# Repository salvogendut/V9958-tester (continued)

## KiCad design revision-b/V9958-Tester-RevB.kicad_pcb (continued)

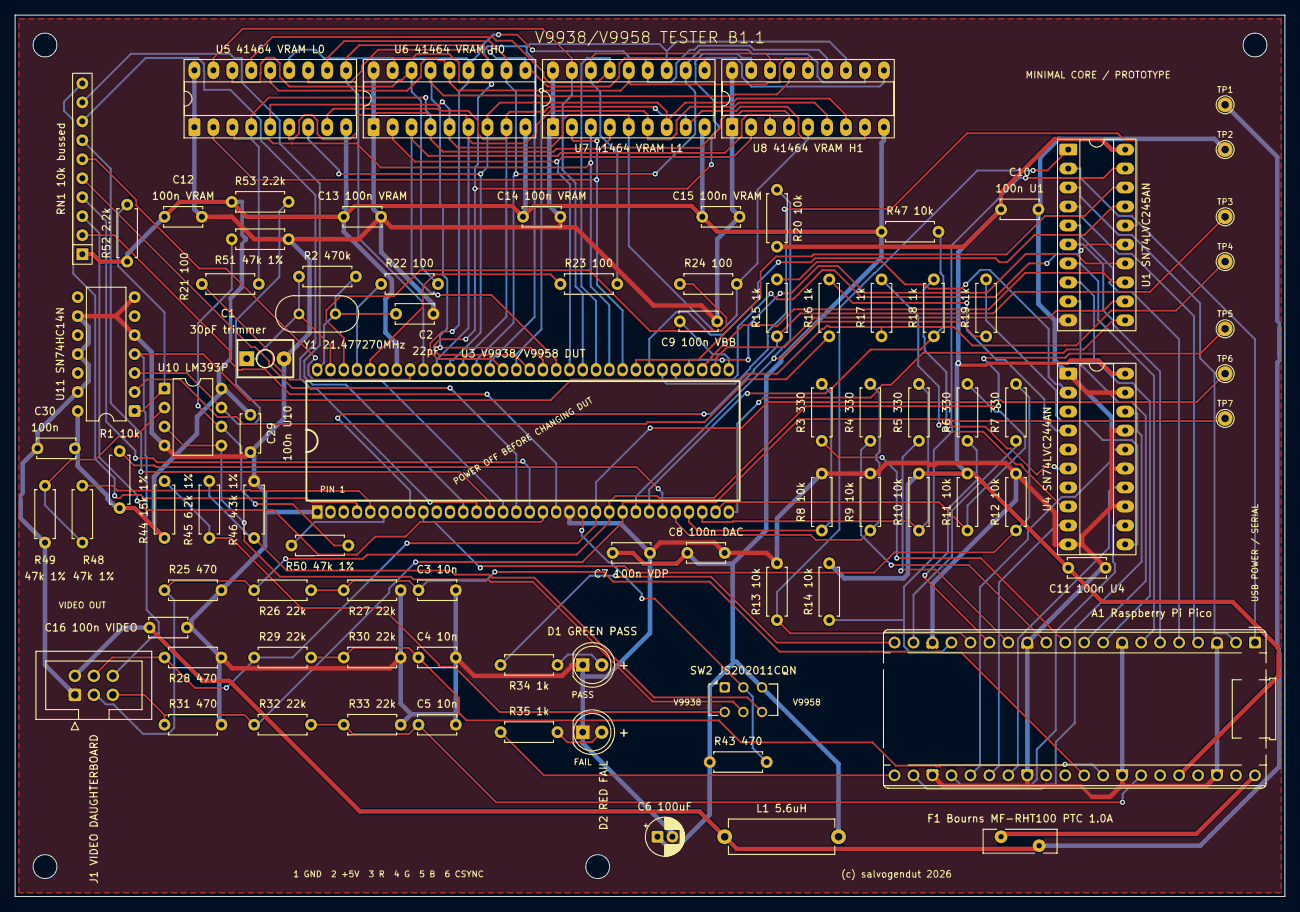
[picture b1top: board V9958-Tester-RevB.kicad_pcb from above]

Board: 2 copper layers, 170.0 x 118.0 mm, 93 parts (0 on the bottom side), 105 nets.

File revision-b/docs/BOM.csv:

Quantity,References,Value / part,KiCad footprint
1,A1,Raspberry Pi Pico,Module:RaspberryPi_Pico_Common_THT
1,C1,30pF trimmer,V9958-Tester:C_Trim_P5.00mm
1,C10,100n U1,Capacitor_THT:C_Disc_D5.0mm_W2.5mm_P5.00mm
1,C11,100n U4,Capacitor_THT:C_Disc_D5.0mm_W2.5mm_P5.00mm
4,C12 C13 C14 C15,100n VRAM,Capacitor_THT:C_Disc_D5.0mm_W2.5mm_P5.00mm
1,C16,100n VIDEO,Capacitor_THT:C_Disc_D5.0mm_W2.5mm_P5.00mm
1,C2,22pF,Capacitor_THT:C_Disc_D5.0mm_W2.5mm_P5.00mm
1,C29,100n U10,Capacitor_THT:C_Disc_D5.0mm_W2.5mm_P5.00mm
3,C3 C4 C5,10n,Capacitor_THT:C_Disc_D5.0mm_W2.5mm_P5.00mm
1,C30,100n,Capacitor_THT:C_Disc_D5.0mm_W2.5mm_P5.00mm
1,C6,100uF,Capacitor_THT:CP_Radial_D5.0mm_P2.00mm
1,C7,100n VDP,Capacitor_THT:C_Disc_D5.0mm_W2.5mm_P5.00mm
1,C8,100n DAC,Capacitor_THT:C_Disc_D5.0mm_W2.5mm_P5.00mm
1,C9,100n VBB,Capacitor_THT:C_Disc_D5.0mm_W2.5mm_P5.00mm
1,D1,GREEN PASS,LED_THT:LED_D5.0mm
1,D2,RED FAIL,LED_THT:LED_D5.0mm
1,F1,Bourns MF-RHT100 PTC 1.0A,Fuse:Fuse_Bourns_MF-RHT100
1,J1,VIDEO DAUGHTERBOARD,Connector_IDC:IDC-Header_2x03_P2.54mm_Vertical
1,L1,5.6uH,Inductor_THT:L_Axial_L14.0mm_D4.5mm_P15.24mm_Horizontal_Fastron_LACC
10,R1 R8 R9 R10 R11 R12 R13 R14 R20 R47,10k,Resistor_THT:R_Axial_DIN0207_L6.3mm_D2.5mm_P7.62mm_Horizontal
7,R15 R16 R17 R18 R19 R34 R35,1k,Resistor_THT:R_Axial_DIN0207_L6.3mm_D2.5mm_P7.62mm_Horizontal
1,R2,470k,Resistor_THT:R_Axial_DIN0207_L6.3mm_D2.5mm_P7.62mm_Horizontal
4,R21 R22 R23 R24,100,Resistor_THT:R_Axial_DIN0207_L6.3mm_D2.5mm_P7.62mm_Horizontal
4,R25 R28 R31 R43,470,Resistor_THT:R_Axial_DIN0207_L6.3mm_D2.5mm_P7.62mm_Horizontal
6,R26 R27 R29 R30 R32 R33,22k,Resistor_THT:R_Axial_DIN0207_L6.3mm_D2.5mm_P7.62mm_Horizontal
5,R3 R4 R5 R6 R7,330,Resistor_THT:R_Axial_DIN0207_L6.3mm_D2.5mm_P7.62mm_Horizontal
1,R44,15k 1%,Resistor_THT:R_Axial_DIN0207_L6.3mm_D2.5mm_P7.62mm_Horizontal
1,R45,6.2k 1%,Resistor_THT:R_Axial_DIN0207_L6.3mm_D2.5mm_P7.62mm_Horizontal
1,R46,4.3k 1%,Resistor_THT:R_Axial_DIN0207_L6.3mm_D2.5mm_P7.62mm_Horizontal
4,R48 R49 R50 R51,47k 1%,Resistor_THT:R_Axial_DIN0207_L6.3mm_D2.5mm_P7.62mm_Horizontal
2,R52 R53,2.2k,Resistor_THT:R_Axial_DIN0207_L6.3mm_D2.5mm_P7.62mm_Horizontal
1,RN1,10k bussed,Resistor_THT:R_Array_SIP10
1,SW2,JS202011CQN,Button_Switch_THT:SW_CK_JS202011CQN_DPDT_Straight
1,U1,SN74LVC245AN,Package_DIP:DIP-20_W7.62mm_Socket_LongPads
1,U10,LM393P,Package_DIP:DIP-8_W7.62mm
1,U11,SN74HC14N,Package_DIP:DIP-14_W7.62mm
1,U3,V9938/V9958 DUT,V9958-Tester:SDIP-64_W19.05mm_P1.778mm_Socket
1,U4,SN74LVC244AN,Package_DIP:DIP-20_W7.62mm_Socket_LongPads
1,U5,41464 VRAM L0,Package_DIP:DIP-18_W7.62mm_Socket_LongPads
1,U6,41464 VRAM H0,Package_DIP:DIP-18_W7.62mm_Socket_LongPads
1,U7,41464 VRAM L1,Package_DIP:DIP-18_W7.62mm_Socket_LongPads
1,U8,41464 VRAM H1,Package_DIP:DIP-18_W7.62mm_Socket_LongPads
1,Y1,21.477270MHz,Crystal:Crystal_HC49-U_Vertical

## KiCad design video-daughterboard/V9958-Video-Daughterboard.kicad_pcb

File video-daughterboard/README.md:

# V9958 RGB DIN daughterboard

This optional all-through-hole 120 x 80 mm board moves the CXA1645P RGB cable
drivers and Omega-compatible DIN-8 connector away from the minimal Revision B
tester core.

J1 uses a keyed straight-through 2x3 IDC cable: 1 GND, 2 +5 V, 3 red, 4 green,
5 blue and 6 CSYNC. J2 faces out through the top board edge on daughterboard B1.
Fit a Same Sky **SDS-80J**, a standard full-size 270° right-angle DIN-8 socket.
The shielded SDF-80J with a date code after 03/03/2022 shares the PCB hole pattern. [SDS-80J drawing, p. 5](https://www.sameskydevices.com/product/resource/sds-j.pdf) · [DigiKey Italy](https://www.digikey.it/it/products/detail/same-sky-formerly-cui-devices/SDS-80J/97041)

J2 follows the Omega RGB assignments: pin 1 GND, pin 3 AV
control, pin 4 composite sync, pin 5 RGB/YS control, pin 6 red, pin 7 green and
pin 8 blue. Pin 2 is unconnected because the tester has no audio source.

The output is native 15.6 kHz PAL RGB, not VGA. The board does not create
composite video; J2 pin 4 is sync only. See the [schematic PDF](docs/V9958-Video-Daughterboard-Schematic.pdf),
[BOM](docs/BOM.csv), [test procedure](docs/TEST-PROCEDURE.md) and
[validation record](docs/VALIDATION.md). This remains an unbuilt prototype.

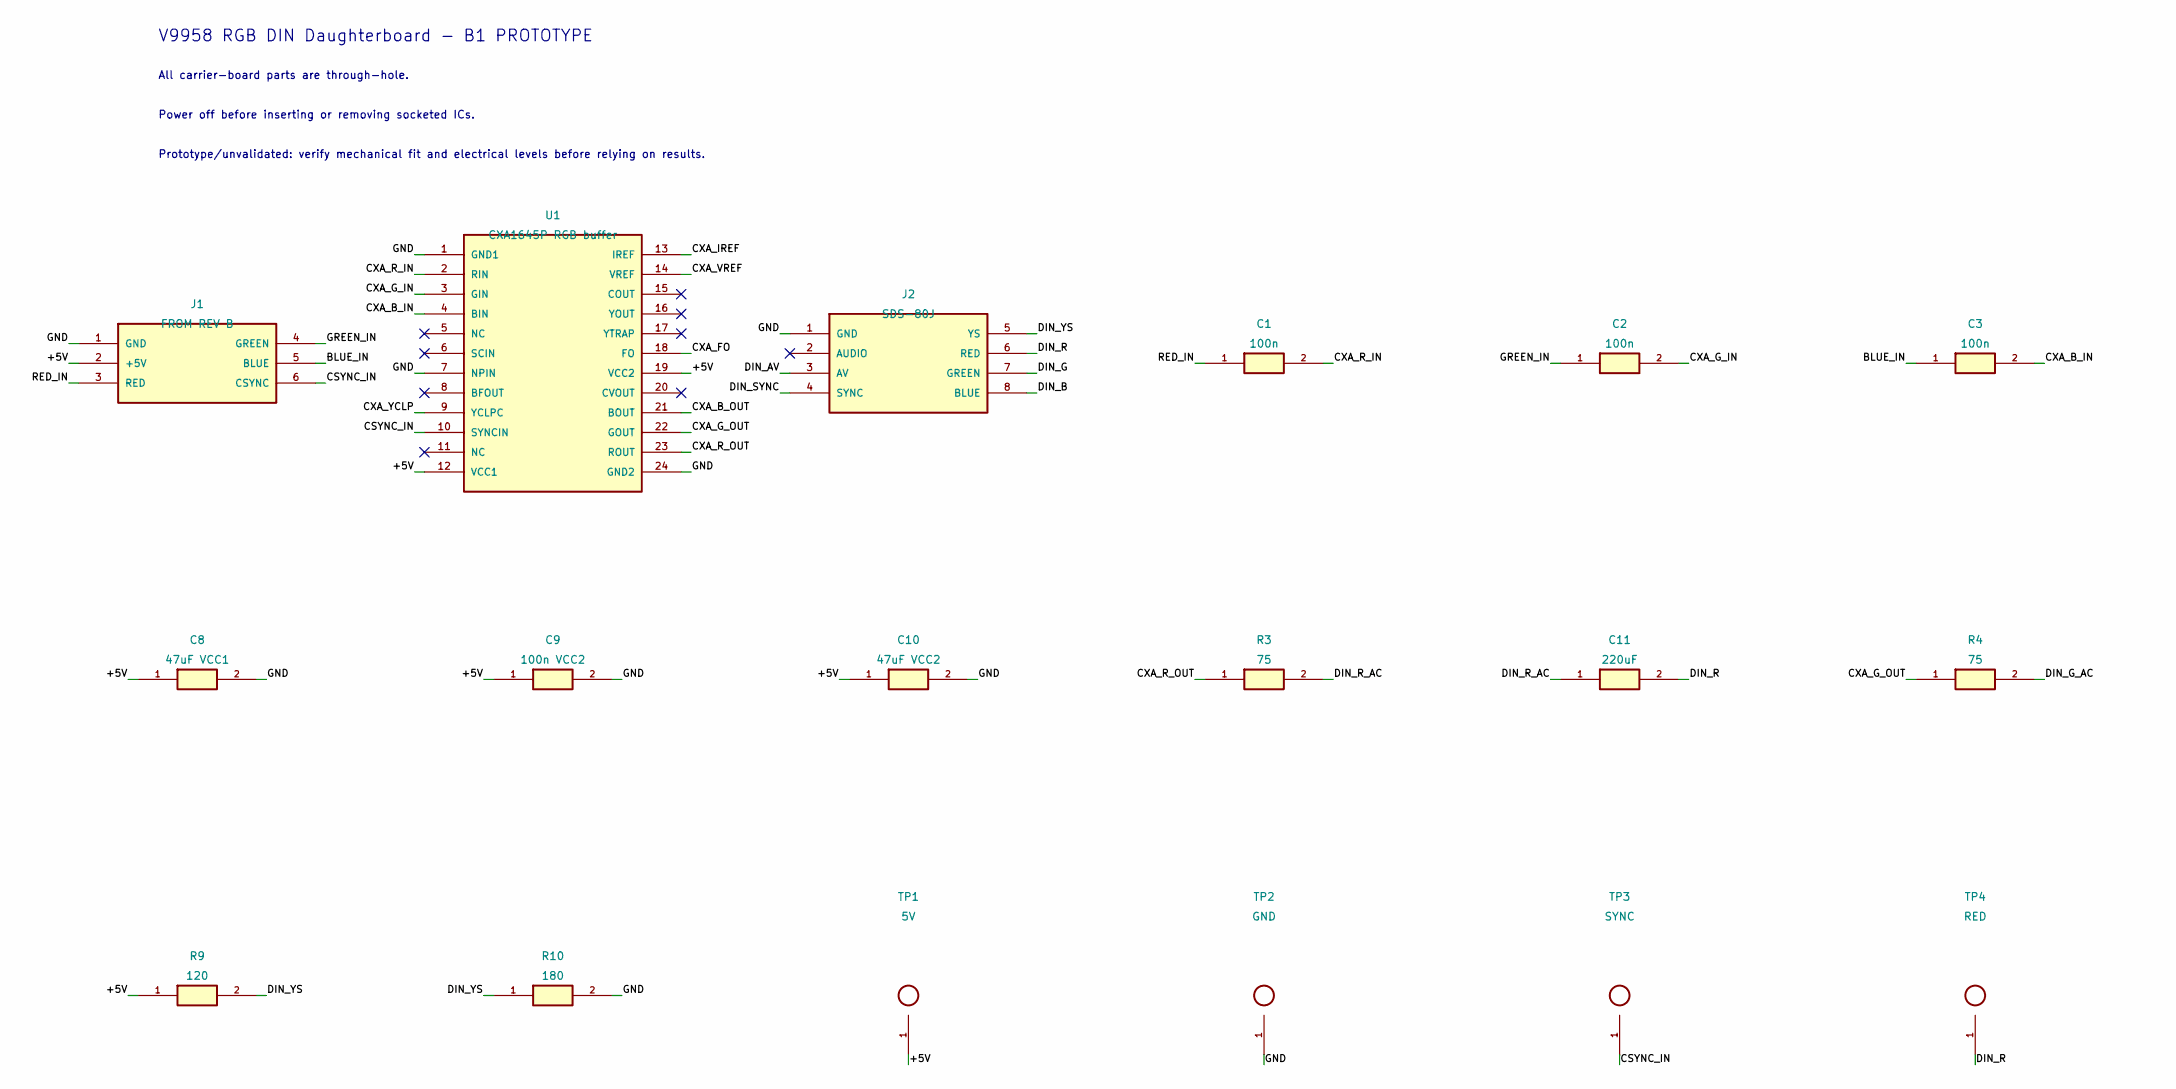
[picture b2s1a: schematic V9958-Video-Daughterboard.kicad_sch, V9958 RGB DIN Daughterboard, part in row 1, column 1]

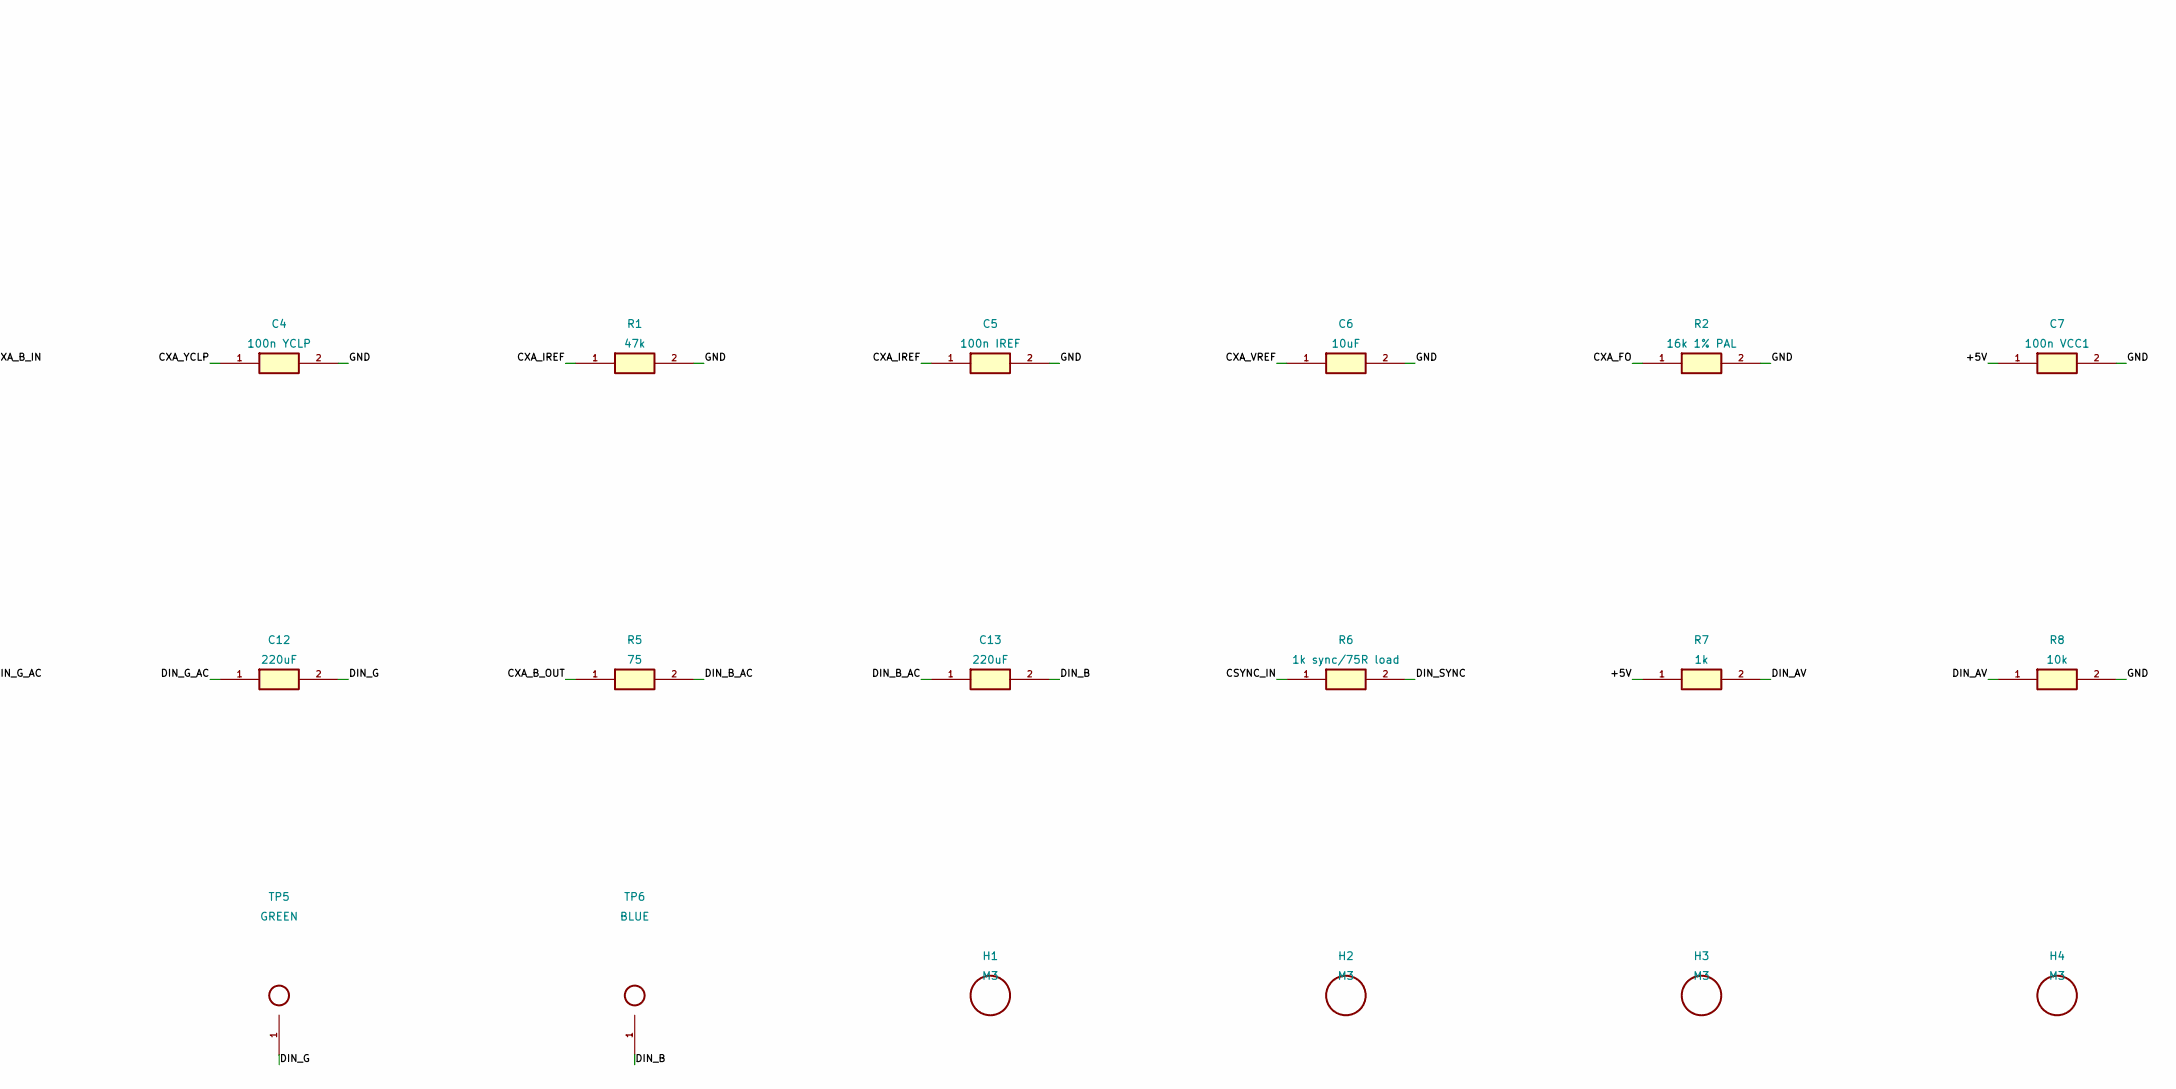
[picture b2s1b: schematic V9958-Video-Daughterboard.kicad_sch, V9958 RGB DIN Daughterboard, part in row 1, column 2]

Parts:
C1, C2, C3: 100n; C_Disc_D5.0mm_W2.5mm_P5.00mm
C4: 100n YCLP; C_Disc_D5.0mm_W2.5mm_P5.00mm
C5: 100n IREF; C_Disc_D5.0mm_W2.5mm_P5.00mm
C6: 10uF; CP_Radial_D5.0mm_P2.00mm
C7: 100n VCC1; C_Disc_D5.0mm_W2.5mm_P5.00mm
C8: 47uF VCC1; CP_Radial_D5.0mm_P2.00mm
C9: 100n VCC2; C_Disc_D5.0mm_W2.5mm_P5.00mm
C10: 47uF VCC2; CP_Radial_D5.0mm_P2.00mm
C11, C12, C13: 220uF; CP_Radial_D8.0mm_P3.50mm
H1, H2, H3, H4: M3; MountingHole_3.2mm_M3
J1: FROM REV B; IDC-Header_2x03_P2.54mm_Vertical
J2: SDS-80J; DIN-8_SameSky_SDS-80J
R1: 47k; R_Axial_DIN0207_L6.3mm_D2.5mm_P7.62mm_Horizontal
R2: 16k 1% PAL; R_Axial_DIN0207_L6.3mm_D2.5mm_P7.62mm_Horizontal
R3, R4, R5: 75; R_Axial_DIN0207_L6.3mm_D2.5mm_P7.62mm_Horizontal
R6: 1k sync/75R load; R_Axial_DIN0207_L6.3mm_D2.5mm_P7.62mm_Horizontal
R7: 1k; R_Axial_DIN0207_L6.3mm_D2.5mm_P7.62mm_Horizontal
R8: 10k; R_Axial_DIN0207_L6.3mm_D2.5mm_P7.62mm_Horizontal
R9: 120; R_Axial_DIN0207_L6.3mm_D2.5mm_P7.62mm_Horizontal
R10: 180; R_Axial_DIN0207_L6.3mm_D2.5mm_P7.62mm_Horizontal
TP1: 5V; TestPoint_THTPad_D2.0mm_Drill1.0mm
TP2: GND; TestPoint_THTPad_D2.0mm_Drill1.0mm
TP3: SYNC; TestPoint_THTPad_D2.0mm_Drill1.0mm
TP4: RED; TestPoint_THTPad_D2.0mm_Drill1.0mm
TP5: GREEN; TestPoint_THTPad_D2.0mm_Drill1.0mm
TP6: BLUE; TestPoint_THTPad_D2.0mm_Drill1.0mm
U1: CXA1645P RGB buffer; DIP-24_W10.16mm_Socket_LongPads

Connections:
/+5V: C7.1, C8.1, C9.1, C10.1, J1.2 (+5V), R7.1, R9.1, TP1.1, U1.12 (VCC1), U1.19 (VCC2)
/BLUE_IN: C3.1, J1.5 (BLUE)
/CSYNC_IN: J1.6 (CSYNC), R6.1, TP3.1, U1.10 (SYNCIN)
/CXA_B_IN: C3.2, U1.4 (BIN)
/CXA_B_OUT: R5.1, U1.21 (BOUT)
/CXA_FO: R2.1, U1.18 (FO)
/CXA_G_IN: C2.2, U1.3 (GIN)
/CXA_G_OUT: R4.1, U1.22 (GOUT)
/CXA_IREF: C5.1, R1.1, U1.13 (IREF)
/CXA_R_IN: C1.2, U1.2 (RIN)
/CXA_R_OUT: R3.1, U1.23 (ROUT)
/CXA_VREF: C6.1, U1.14 (VREF)
/CXA_YCLP: C4.1, U1.9 (YCLPC)
/DIN_AV: J2.3 (AV), R7.2, R8.1
/DIN_B: C13.2, J2.8 (BLUE), TP6.1
/DIN_B_AC: C13.1, R5.2
/DIN_G: C12.2, J2.7 (GREEN), TP5.1
/DIN_G_AC: C12.1, R4.2
/DIN_R: C11.2, J2.6 (RED), TP4.1
/DIN_R_AC: C11.1, R3.2
/DIN_SYNC: J2.4 (SYNC), R6.2
/DIN_YS: J2.5 (YS), R9.2, R10.1
/GND: C4.2, C5.2, C6.2, C7.2, C8.2, C9.2, C10.2, J1.1 (GND), J2.1 (GND), R1.2, R2.2, R8.2, R10.2, TP2.1, U1.1 (GND1), U1.7 (NPIN), U1.24 (GND2)
/GREEN_IN: C2.1, J1.4 (GREEN)
/RED_IN: C1.1, J1.3 (RED)

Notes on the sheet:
V9958 RGB DIN Daughterboard - B1 PROTOTYPE
All carrier-board parts are through-hole.
Power off before inserting or removing socketed ICs.
Prototype/unvalidated: verify mechanical fit and electrical levels before relying on results.

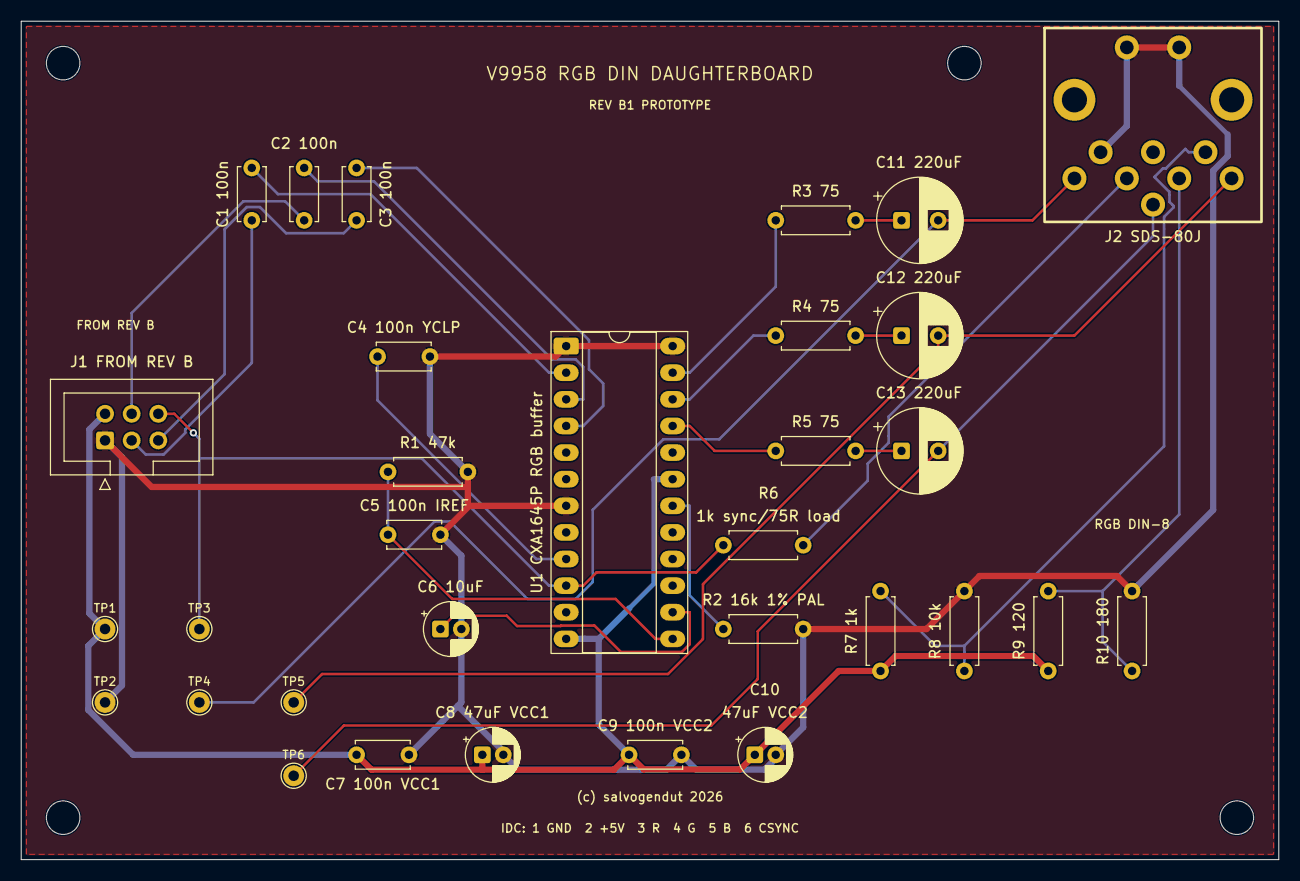
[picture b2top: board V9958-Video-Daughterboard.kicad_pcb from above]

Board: 2 copper layers, 120.0 x 80.0 mm, 36 parts (0 on the bottom side), 25 nets.

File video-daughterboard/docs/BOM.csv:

Quantity,References,Value / part,KiCad footprint
3,C1 C2 C3,100n,Capacitor_THT:C_Disc_D5.0mm_W2.5mm_P5.00mm
1,C10,47uF VCC2,Capacitor_THT:CP_Radial_D5.0mm_P2.00mm
3,C11 C12 C13,220uF,Capacitor_THT:CP_Radial_D8.0mm_P3.50mm
1,C4,100n YCLP,Capacitor_THT:C_Disc_D5.0mm_W2.5mm_P5.00mm
1,C5,100n IREF,Capacitor_THT:C_Disc_D5.0mm_W2.5mm_P5.00mm
1,C6,10uF,Capacitor_THT:CP_Radial_D5.0mm_P2.00mm
1,C7,100n VCC1,Capacitor_THT:C_Disc_D5.0mm_W2.5mm_P5.00mm
1,C8,47uF VCC1,Capacitor_THT:CP_Radial_D5.0mm_P2.00mm
1,C9,100n VCC2,Capacitor_THT:C_Disc_D5.0mm_W2.5mm_P5.00mm
1,J1,FROM REV B,Connector_IDC:IDC-Header_2x03_P2.54mm_Vertical
1,J2,SDS-80J,V9958-Video-Daughterboard:DIN-8_SameSky_SDS-80J
1,R1,47k,Resistor_THT:R_Axial_DIN0207_L6.3mm_D2.5mm_P7.62mm_Horizontal
1,R10,180,Resistor_THT:R_Axial_DIN0207_L6.3mm_D2.5mm_P7.62mm_Horizontal
1,R2,16k 1% PAL,Resistor_THT:R_Axial_DIN0207_L6.3mm_D2.5mm_P7.62mm_Horizontal
3,R3 R4 R5,75,Resistor_THT:R_Axial_DIN0207_L6.3mm_D2.5mm_P7.62mm_Horizontal
1,R6,1k sync/75R load,Resistor_THT:R_Axial_DIN0207_L6.3mm_D2.5mm_P7.62mm_Horizontal
1,R7,1k,Resistor_THT:R_Axial_DIN0207_L6.3mm_D2.5mm_P7.62mm_Horizontal
1,R8,10k,Resistor_THT:R_Axial_DIN0207_L6.3mm_D2.5mm_P7.62mm_Horizontal
1,R9,120,Resistor_THT:R_Axial_DIN0207_L6.3mm_D2.5mm_P7.62mm_Horizontal
1,U1,CXA1645P RGB buffer,Package_DIP:DIP-24_W10.16mm_Socket_LongPads

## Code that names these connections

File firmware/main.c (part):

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    PIN_MODE1 = 9,
    PIN_CSW_N = 10,
    PIN_CSR_N = 11,
    PIN_BUS_DIR = 12,
    PIN_BUS_OE_N = 13,
    PIN_VDP_RESET_N = 14,
    PIN_LED_GREEN = 15,
    PIN_LED_RED = 16,
    PIN_CPUCLK = 17,
    PIN_WAIT_N = 18,
    PIN_HSYNC_N = 19,
    PIN_INT_N = 20,
    PIN_CSYNC_N = 21,
    PIN_TEST_N = 22,
    PIN_ADC_R = 26,
    PIN_ADC_G = 27,
    PIN_ADC_B = 28,
};

#define DATA_MASK 0x000000ffu
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static void controls_idle(void) {
    gpio_put(PIN_CSW_N, 1);
    gpio_put(PIN_CSR_N, 1);
    gpio_put(PIN_BUS_OE_N, 1);
    gpio_put(PIN_MODE0, 0);
    gpio_put(PIN_MODE1, 0);
}
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    controls_idle();
    if (!wait_ready_us(100)) return false;
    set_port(port);
    gpio_put(PIN_BUS_DIR, 1);             /* LVC245 A (Pico) -> B (VDP). */
    gpio_set_dir_out_masked(DATA_MASK);
    gpio_put_masked(DATA_MASK, value);
    gpio_put(PIN_BUS_OE_N, 0);
    busy_wait_us_32(1);
    uint32_t irq_state = save_and_disable_interrupts();
    gpio_put(PIN_CSW_N, 0);
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    restore_interrupts(irq_state);
    /* 8 us also satisfies the longest documented inter-byte high time. */
    busy_wait_us_32(8);
    gpio_put(PIN_BUS_OE_N, 1);
    gpio_set_dir_in_masked(DATA_MASK);
    return wait_ready_us(100);
}
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    controls_idle();
    if (!wait_ready_us(100)) return false;
    set_port(port);
    gpio_put(PIN_BUS_DIR, 0);             /* LVC245 B (VDP) -> A (Pico). */
    gpio_set_dir_in_masked(DATA_MASK);
    gpio_put(PIN_BUS_OE_N, 0);
    busy_wait_us_32(1);
    uint32_t irq_state = save_and_disable_interrupts();
    gpio_put(PIN_CSR_N, 0);
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    gpio_put(PIN_CSR_N, 1);
    restore_interrupts(irq_state);
    busy_wait_us_32(8);
    gpio_put(PIN_BUS_OE_N, 1);
    return wait_ready_us(100);
}

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
static enum test_error run_test(void) {
    model = VDP_UNKNOWN;
    gpio_put(PIN_LED_GREEN, 0);
    gpio_put(PIN_LED_RED, 0);
    controls_idle();
    gpio_put(PIN_VDP_RESET_N, 0);
    sleep_ms(20);
    gpio_put(PIN_VDP_RESET_N, 1);
    sleep_ms(50);

    /* PAL, standard sync (S0=1) makes pin 5 horizontal sync during this
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static void init_pins(void) {
    for (uint pin = 0; pin <= 22; ++pin) gpio_init(pin);
    gpio_set_dir_in_masked(DATA_MASK);
    for (uint pin = PIN_MODE0; pin <= PIN_LED_RED; ++pin) gpio_set_dir(pin, GPIO_OUT);
    for (uint pin = PIN_CPUCLK; pin <= PIN_TEST_N; ++pin) gpio_set_dir(pin, GPIO_IN);
    gpio_pull_up(PIN_TEST_N);
    controls_idle();
    gpio_put(PIN_BUS_DIR, 0);
    gpio_put(PIN_VDP_RESET_N, 0);
    gpio_put(PIN_LED_GREEN, 0);
    gpio_put(PIN_LED_RED, 0);
    adc_init();
    adc_gpio_init(PIN_ADC_R);
    adc_gpio_init(PIN_ADC_G);
    adc_gpio_init(PIN_ADC_B);
}

static void test_and_report(void) {
    enum test_error result = run_test();
    gpio_put(PIN_LED_GREEN, result == ERR_NONE);
    gpio_put(PIN_LED_RED, result != ERR_NONE);
    if (result == ERR_NONE)
        printf("RESULT: %s PASS (code 0)\n", model_name());
    else
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
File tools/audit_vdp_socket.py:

#!/usr/bin/env python3
"""Check the two switch positions and DIN mating geometry on the released boards."""
from itertools import product
from pathlib import Path
import xml.etree.ElementTree as ET

import pcbnew
from polarity import check_polarity

ROOT = Path(__file__).resolve().parents[1]


def check_sync_thresholds(values):
    # TI LM393P input offset and bias, allowing for both inputs on the shared
    # reference ladder. Resistances below are in kΩ and voltages are in V.
    for top_ref, bottom_ref in (("R48", "R49"), ("R50", "R51")):
        refs = ("R44", "R45", "R46", top_ref, bottom_ref)
        nominal = [float(values[ref].removesuffix("k 1%")) for ref in refs]
        for factors in product((0.99, 1.01), repeat=5):
            r44, r45, r46, top, bottom = [r * k for r, k in zip(nominal, factors)]
            gain = bottom / (top + bottom)
            total = r44 + r45 + r46
            for rail in (4.75, 5.25):
                assert rail * gain + 0.010 < rail - 2.0  # input headroom at full-scale
                for lower, low_max, high_min in ((r45 + r46, 3.7, 4.5), (r46, 0.8, 2.2)):
                    reference = rail * lower / total
                    reference_r = lower * (total - lower) / total
                    error = 0.009 + 0.0004 * (top * gain + 2 * reference_r)
                    assert error < 0.025
                    assert low_max < (reference - 0.025) / gain
                    assert (reference + 0.025) / gain < high_min


def check_socket(netlist):
    tree = ET.parse(netlist)
    values = {item.get("ref"): item.findtext("value") for item in tree.findall("./components/comp")}
    assert [values[f"R{i}"] for i in range(43, 48)] == ["470", "15k 1%", "6.2k 1%", "4.3k 1%", "10k"]
    assert all(values[f"R{i}"] == "47k 1%" for i in (48, 49, 50, 51))
    assert values["R52"] == values["R53"] == "2.2k"
    assert values["C30"] == "100n" and values["U11"] == "SN74HC14N"
    assert values["U10"] == "LM393P" and values["SW2"] == "JS202011CQN"
    check_sync_thresholds(values)
    pins = {}
    for net in tree.findall("./nets/net"):
        for node in net.findall("node"):
            pins[node.get("ref"), int(node.get("pin"))] = net.get("name").removeprefix("/")
    expected = {
        "VDP_PIN21": {("U3", 21), ("SW2", 2), ("R43", 2)},
        "HSYNC_RAW": {("U3", 5), ("R48", 1)},
        "CSYNC_RAW": {("U3", 6), ("R50", 1)},
        "H_HALF": {("R48", 2), ("R49", 1), ("U10", 2)},
        "C_HALF": {("R50", 2), ("R51", 1), ("U10", 6)},
        "H_COMP": {("U10", 1), ("R52", 2), ("U11", 1)},
        "C_COMP": {("U10", 7), ("R53", 2), ("U11", 3)},
        "SYNC_REF": {("U10", 3), ("U10", 5), ("SW2", 5)},
        "REF_38": {("R44", 2), ("R45", 1), ("SW2", 6)},
        "REF_58": {("R45", 2), ("R46", 1), ("SW2", 4)},
    }
    for net, contacts in expected.items():
        assert {pin for pin, actual in pins.items() if actual == net} == contacts, (netlist, net)
    for pin in [("U3", 58), ("SW2", 3), ("R43", 1), ("R44", 1), ("R47", 1), ("U10", 8),
                ("R52", 1), ("R53", 1), ("U11", 14), ("C29", 1), ("C30", 1)]:
        assert pins[pin] == "VCCVDP", (netlist, pin)
    assert pins["SW2", 1].startswith("unconnected-")
    assert pins["R46", 2] == pins["U10", 4] == "GND"
    assert pins["R47", 2] == pins["U3", 26] == "WAIT_RAW"
    for pin in [("R49", 2), ("R51", 2), ("C29", 2), ("C30", 2)]:
        assert pins[pin] == "GND"
    for pin in (5, 7, 9, 11, 13):
        assert pins["U11", pin] == "GND"
    for pin in (6, 8, 10, 12):
        assert pins["U11", pin].startswith("unconnected-")
    assert pins["U11", 2] == "HSYNC_TTL" and pins["U11", 4] == "CSYNC_TTL"
    # Confirm the driven signals reach the existing 3.3 V monitor buffer.
    for signal, u4pin in (("HSYNC_TTL", 4), ("CSYNC_TTL", 6)):
        destination = pins["U4", u4pin]
        assert any(pins.get((ref, 1)) == signal and pins.get((ref, 2)) == destination
                   for ref in values if ref.startswith("R"))
    if ("U9", 10) in pins:
        assert pins["U9", 10] == pins["R38", 1] == "CSYNC_TTL"
    else:
        assert pins["J1", 6] == "CSYNC_TTL"


def check_din(board, ref):
    socket = board.FindFootprintByReference(ref)
    face = socket.GetPosition().y
    outline = board.GetBoardEdgesBoundingBox()
    assert abs(outline.GetTop() - face) <= pcbnew.FromMM(0.03)
    assert socket.GetOrientationDegrees() == 0 and socket.GetLayer() == pcbnew.F_Cu
    # SDS-J drawing p.5, top view rotated so the plug enters from the top.
    assert socket.GetValue() == "SDS-80J"
    plated = []
    locating = []
    for pad in socket.Pads():
        offset = pad.GetPosition() - socket.GetPosition()
        drill = pad.GetDrillSize()
        assert drill.x == drill.y
        hole = (pcbnew.ToMM(offset.x), pcbnew.ToMM(offset.y), pcbnew.ToMM(drill.x))
        if pad.GetAttribute() == pcbnew.PAD_ATTRIB_NPTH:
            locating.append(hole)
        else:
            plated.append((pad.GetNumber(), *hole))
    assert sorted(locating) == [(-7.5, 7.5, 2.4), (7.5, 7.5, 2.4)]
    assert sorted(plated) == sorted([
        ("1", -2.5, 2.5, 1.3), ("1", 2.5, 2.5, 1.3),  # E ground terminals
        ("1", -5, 12.5, 1.3), ("2", 0, 12.5, 1.3), ("3", 5, 12.5, 1.3),
        ("4", -2.5, 15, 1.3), ("5", 2.5, 15, 1.3), ("6", -7.5, 15, 1.3),
        ("7", 7.5, 15, 1.3), ("8", 0, 17.5, 1.3),
    ])
    for pin, net in {1: "GND", 3: "DIN_AV", 4: "DIN_SYNC", 5: "DIN_YS",
                     6: "DIN_R", 7: "DIN_G", 8: "DIN_B"}.items():
        assert {p.GetNetname() for p in socket.Pads() if p.GetNumber() == str(pin)} == {"/" + net}
    assert socket.FindPadByNumber("2").GetNetname() == f"unconnected-({ref}-AUDIO-Pad2)"


for path in sorted(ROOT.glob("**/*.kicad_pcb")):
    board = pcbnew.LoadBoard(str(path))
    netlist = path.parent / "docs" / path.with_suffix(".xml").name
    check_polarity(board, netlist)
    if path.parent.name == "video-daughterboard":
        check_din(board, "J2")
    else:
        check_socket(netlist)
        if path.parent == ROOT:
            check_din(board, "J1")
    print(f"{path.stem}: passed")

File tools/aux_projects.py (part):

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                  "V9958-Tester:SDIP-64_W19.05mm_P1.778mm_Socket", {
        1:"GND",4:"VRESET",5:"HSYNC_RAW",6:"CSYNC_RAW",8:"CPUCLK_RAW",9:"VDP_RESET_N",
        12:"CB7",13:"CB6",14:"CB5",15:"CB4",16:"CB3",17:"CB2",18:"CB1",19:"CB0",
        20:"GND",21:"VDP_PIN21",22:"GREEN_RAW",23:"RED_RAW",24:"BLUE_RAW",25:"INT_RAW",26:"WAIT_RAW",
        27:"HRESET",28:"VDP_MODE1",29:"VDP_MODE0",30:"VDP_CSW_N",31:"VDP_CSR_N",
        32:"VDP_D7",33:"VBB",34:"VDP_D6",35:"VDP_D5",36:"VDP_D4",37:"VDP_D3",38:"VDP_D2",39:"VDP_D1",40:"VDP_D0",
        41:"VD0",42:"VD1",43:"VD2",44:"VD3",45:"VD4",46:"VD5",47:"VD6",48:"VD7",
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
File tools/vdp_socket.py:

"""Through-hole model selector and dual sync receiver shared by the tester PCBs."""

LM393 = {1: "OUTA", 2: "INA-", 3: "INA+", 4: "GND",
          5: "INB+", 6: "INB-", 7: "OUTB", 8: "V+"}
HC14 = {1: "1A", 2: "1Y", 3: "2A", 4: "2Y", 5: "3A", 6: "3Y", 7: "GND",
          8: "4Y", 9: "4A", 10: "5Y", 11: "5A", 12: "6Y", 13: "6A", 14: "VCC"}
# Column assignments follow KiCad's JS202011CQN footprint, viewed from above.
SELECTOR = {1: "38-A", 2: "COM-A", 3: "58-A", 4: "58-B", 5: "COM-B", 6: "38-B"}

AXIAL = "Resistor_THT:R_Axial_DIN0207_L6.3mm_D2.5mm_P7.62mm_Horizontal"
DISC = "Capacitor_THT:C_Disc_D5.0mm_W2.5mm_P5.00mm"

# R43 remains connected when SW2 is open or in transit. SW2 only bypasses
# R43 in the V9958 position. The other pole selects the sync slicing level.
PARTS = [
    ("SW2", "VDP_Select", "JS202011CQN", "Button_Switch_THT:SW_CK_JS202011CQN_DPDT_Straight",
     {2: "VDP_PIN21", 3: "VCCVDP", 4: "REF_58", 5: "SYNC_REF", 6: "REF_38"}),
    ("U10", "LM393", "LM393P", "Package_DIP:DIP-8_W7.62mm",
     {1: "H_COMP", 2: "H_HALF", 3: "SYNC_REF", 4: "GND",
      5: "SYNC_REF", 6: "C_HALF", 7: "C_COMP", 8: "VCCVDP"}),
    ("R43", "R", "470", AXIAL, {1: "VCCVDP", 2: "VDP_PIN21"}),
    ("R44", "R", "15k 1%", AXIAL, {1: "VCCVDP", 2: "REF_38"}),
    ("R45", "R", "6.2k 1%", AXIAL, {1: "REF_38", 2: "REF_58"}),
    ("R46", "R", "4.3k 1%", AXIAL, {1: "REF_58", 2: "GND"}),
    ("R47", "R", "10k", AXIAL, {1: "VCCVDP", 2: "WAIT_RAW"}),
    ("U11", "74HC14", "SN74HC14N", "Package_DIP:DIP-14_W7.62mm",
     {1: "H_COMP", 2: "HSYNC_TTL", 3: "C_COMP", 4: "CSYNC_TTL",
      5: "GND", 7: "GND", 9: "GND", 11: "GND", 13: "GND", 14: "VCCVDP"}),
    ("C30", "C", "100n", DISC, {1: "VCCVDP", 2: "GND"}),
    ("R48", "R", "47k 1%", AXIAL, {1: "HSYNC_RAW", 2: "H_HALF"}),
    ("R49", "R", "47k 1%", AXIAL, {1: "H_HALF", 2: "GND"}),
    ("R50", "R", "47k 1%", AXIAL, {1: "CSYNC_RAW", 2: "C_HALF"}),
    ("R51", "R", "47k 1%", AXIAL, {1: "C_HALF", 2: "GND"}),
    ("R52", "R", "2.2k", AXIAL, {1: "VCCVDP", 2: "H_COMP"}),
    ("R53", "R", "2.2k", AXIAL, {1: "VCCVDP", 2: "C_COMP"}),
    ("C29", "C", "100n U10", DISC, {1: "VCCVDP", 2: "GND"}),
]
